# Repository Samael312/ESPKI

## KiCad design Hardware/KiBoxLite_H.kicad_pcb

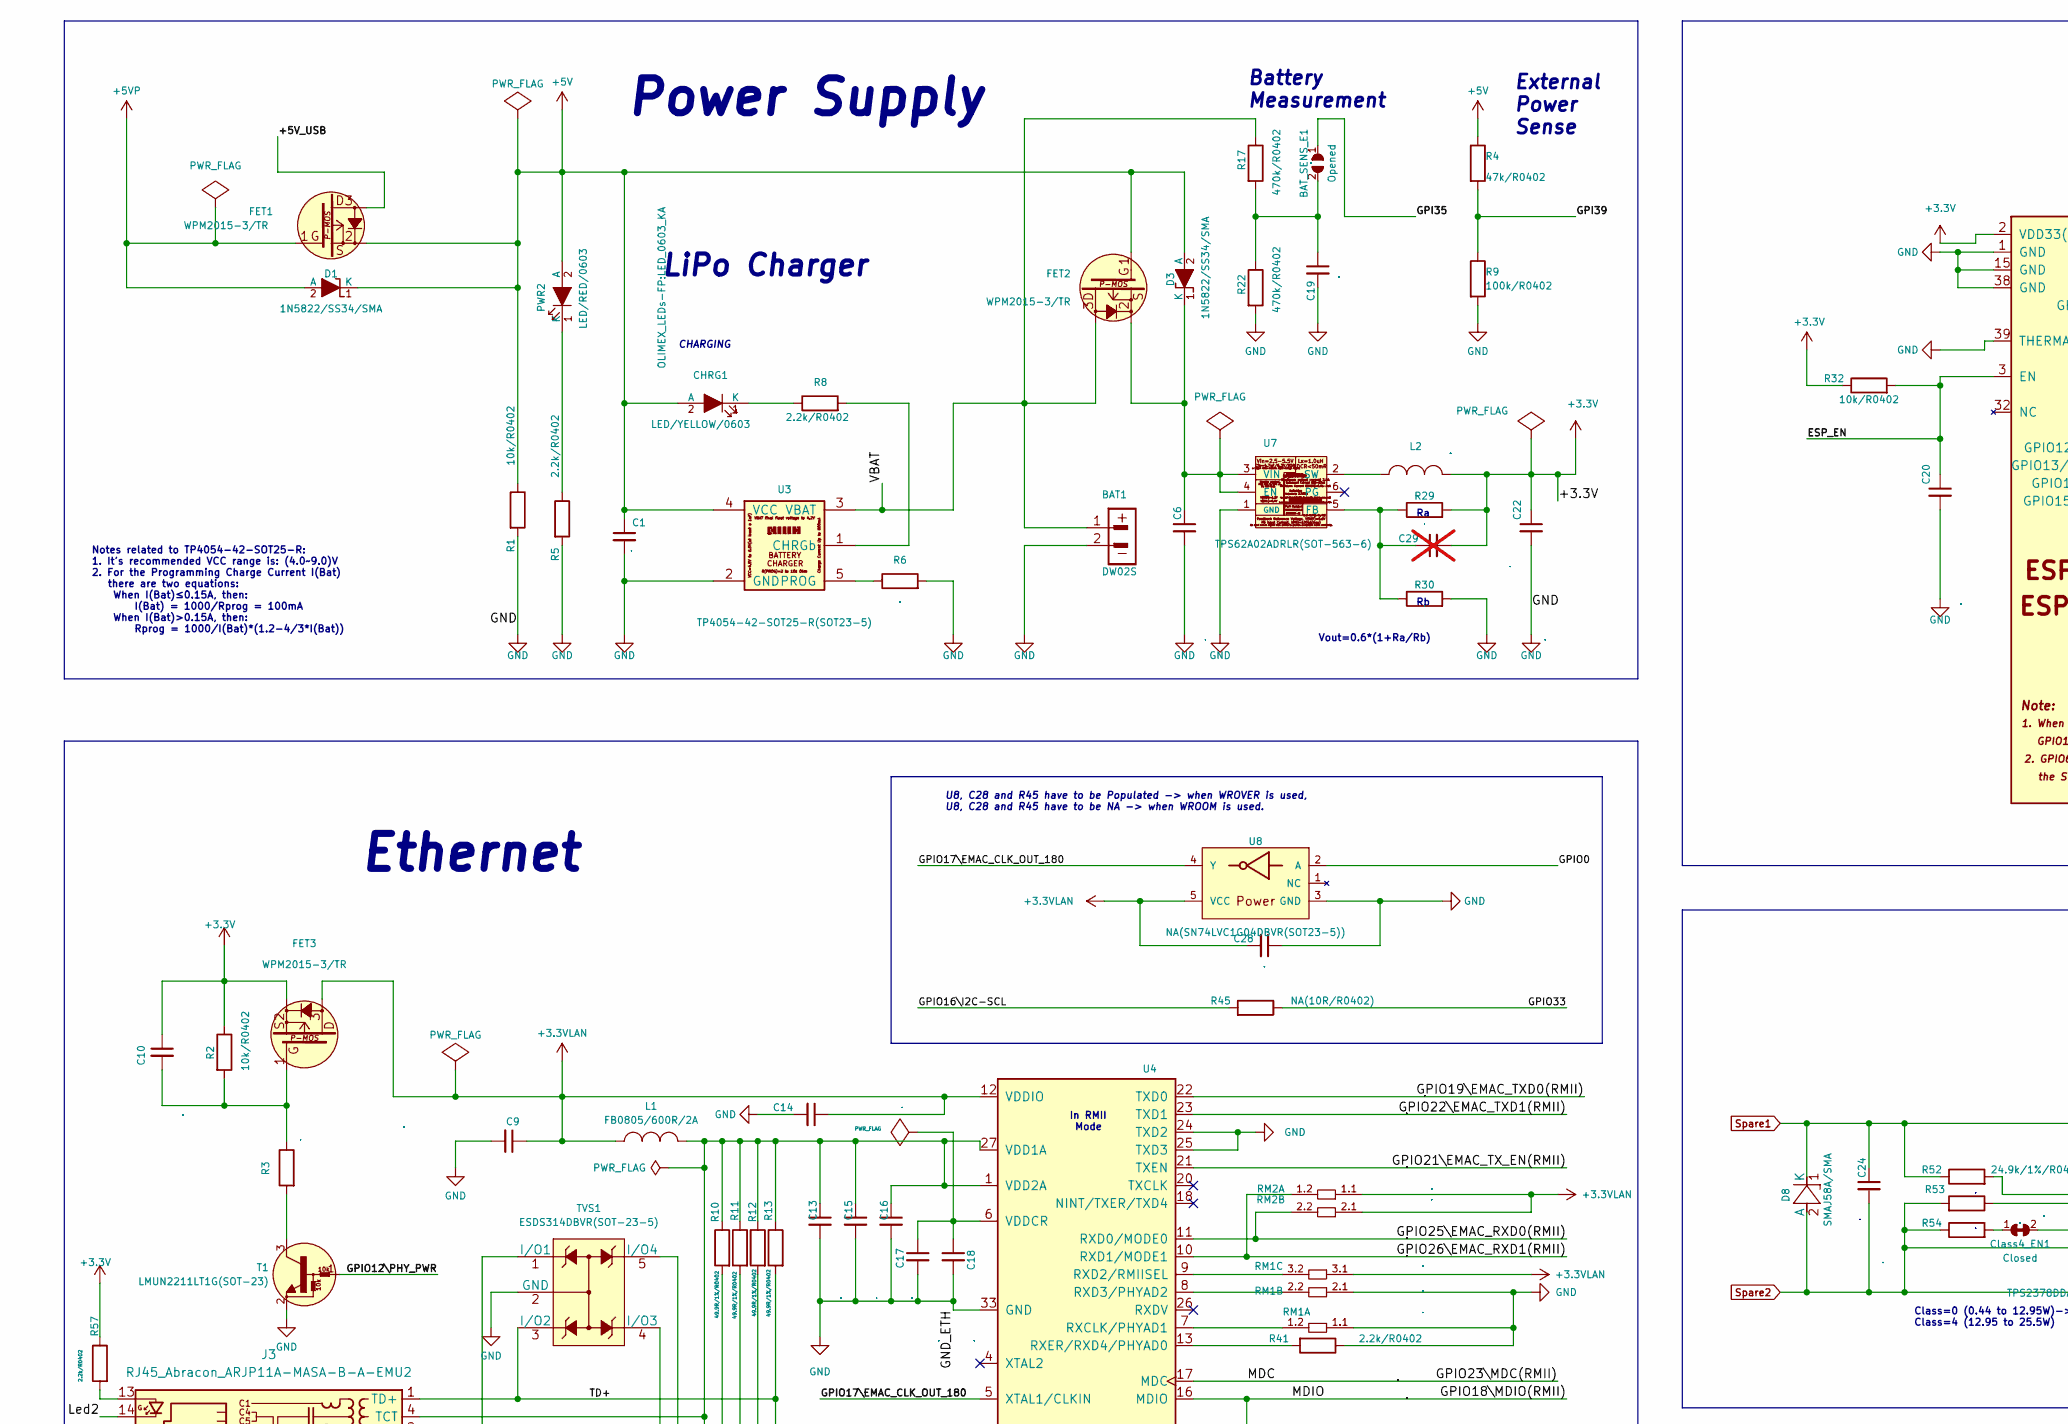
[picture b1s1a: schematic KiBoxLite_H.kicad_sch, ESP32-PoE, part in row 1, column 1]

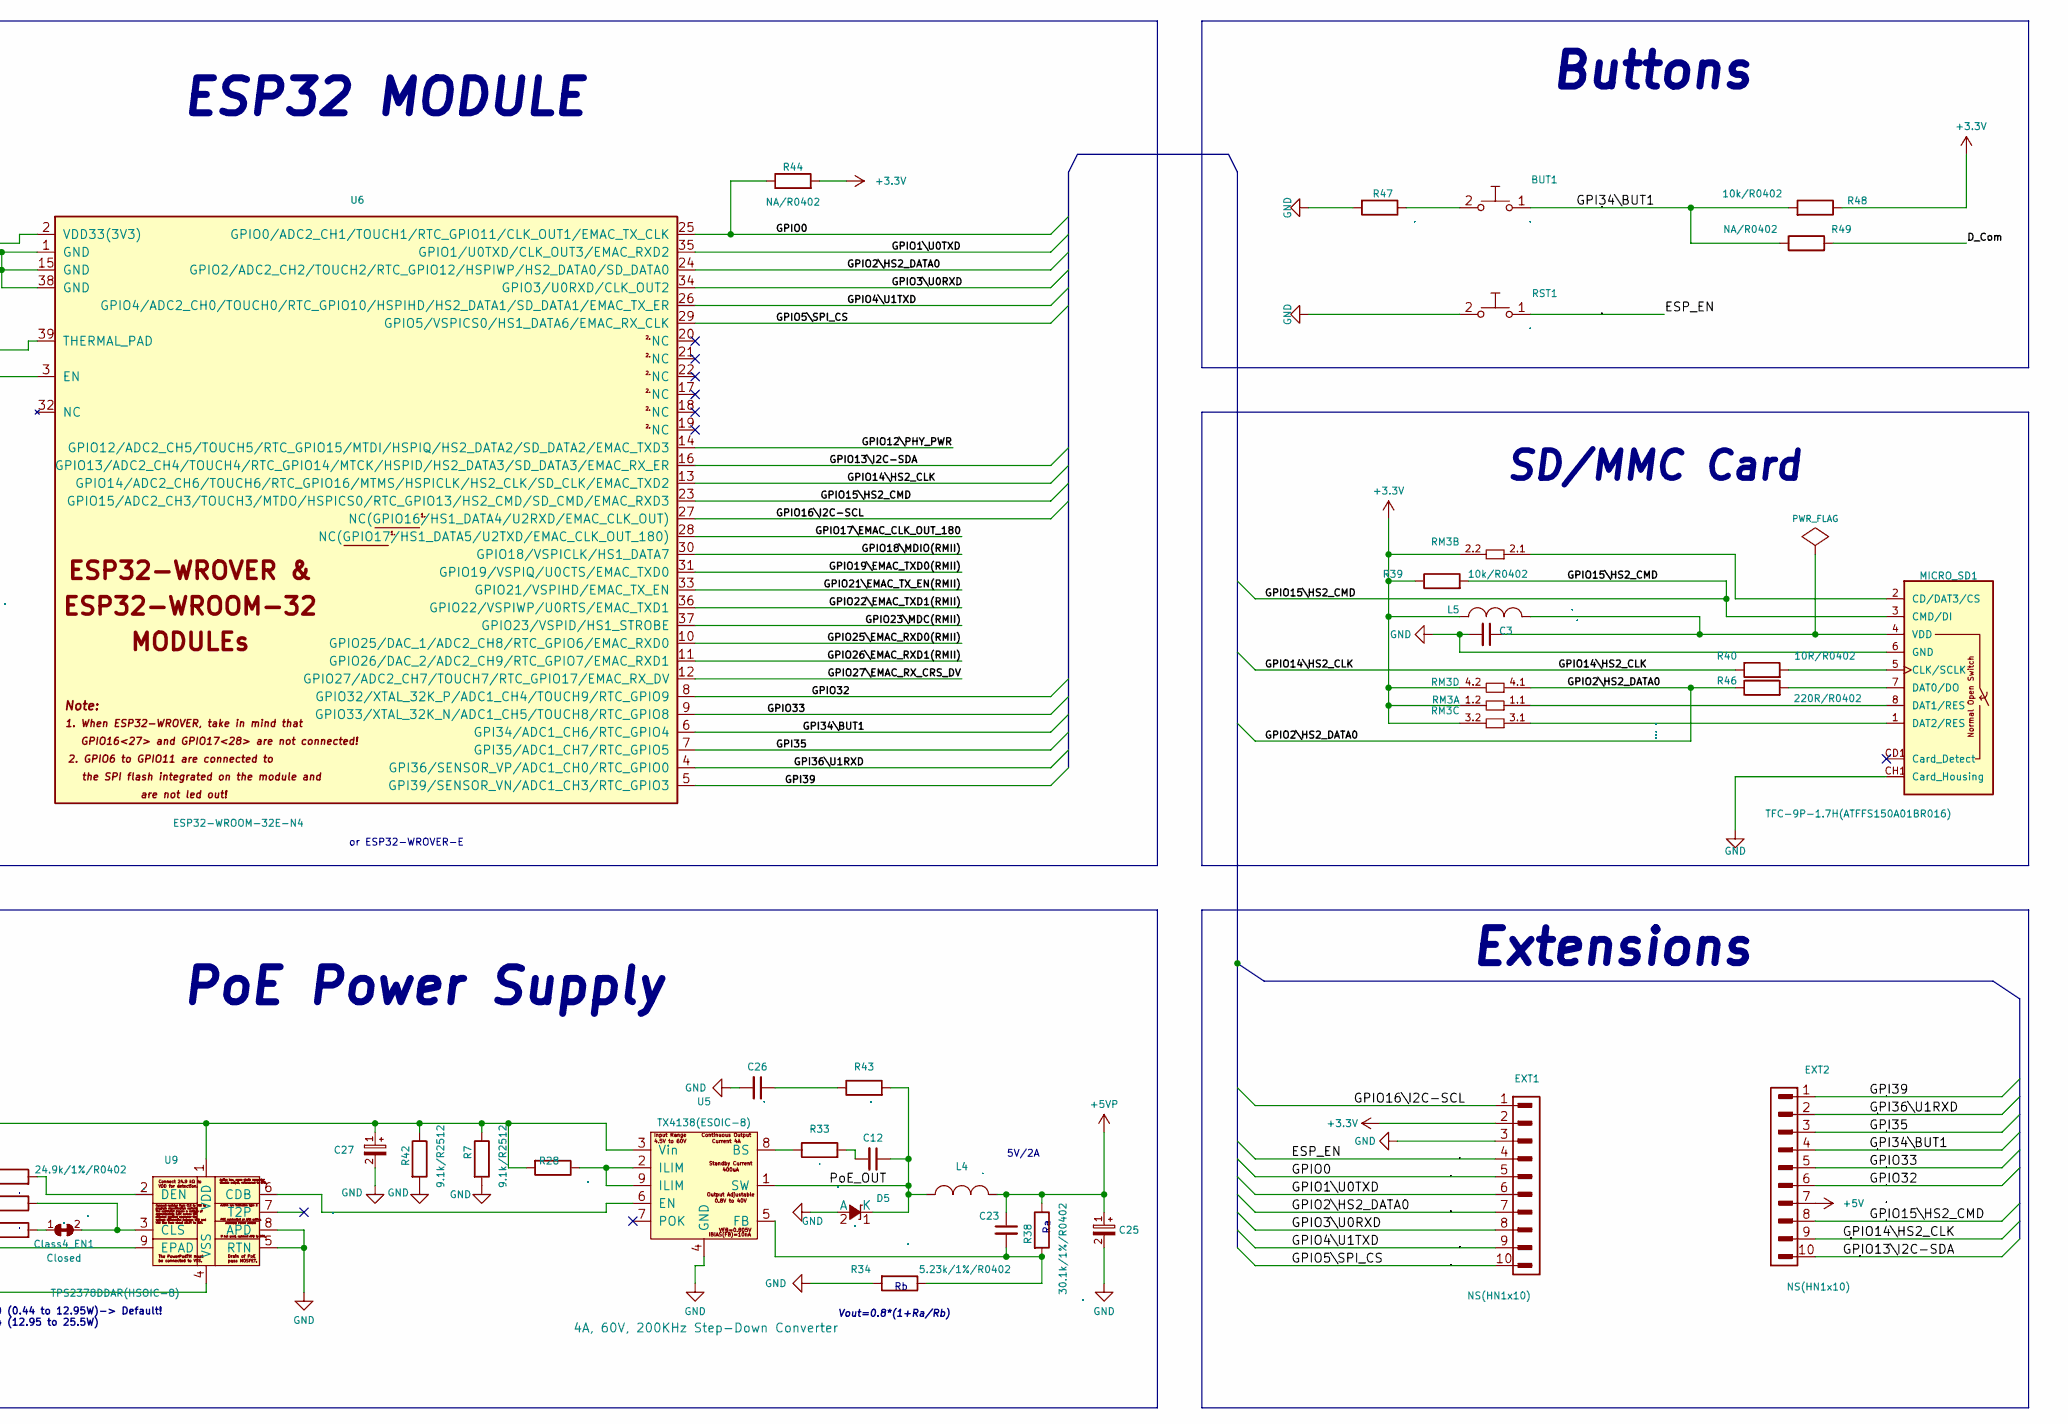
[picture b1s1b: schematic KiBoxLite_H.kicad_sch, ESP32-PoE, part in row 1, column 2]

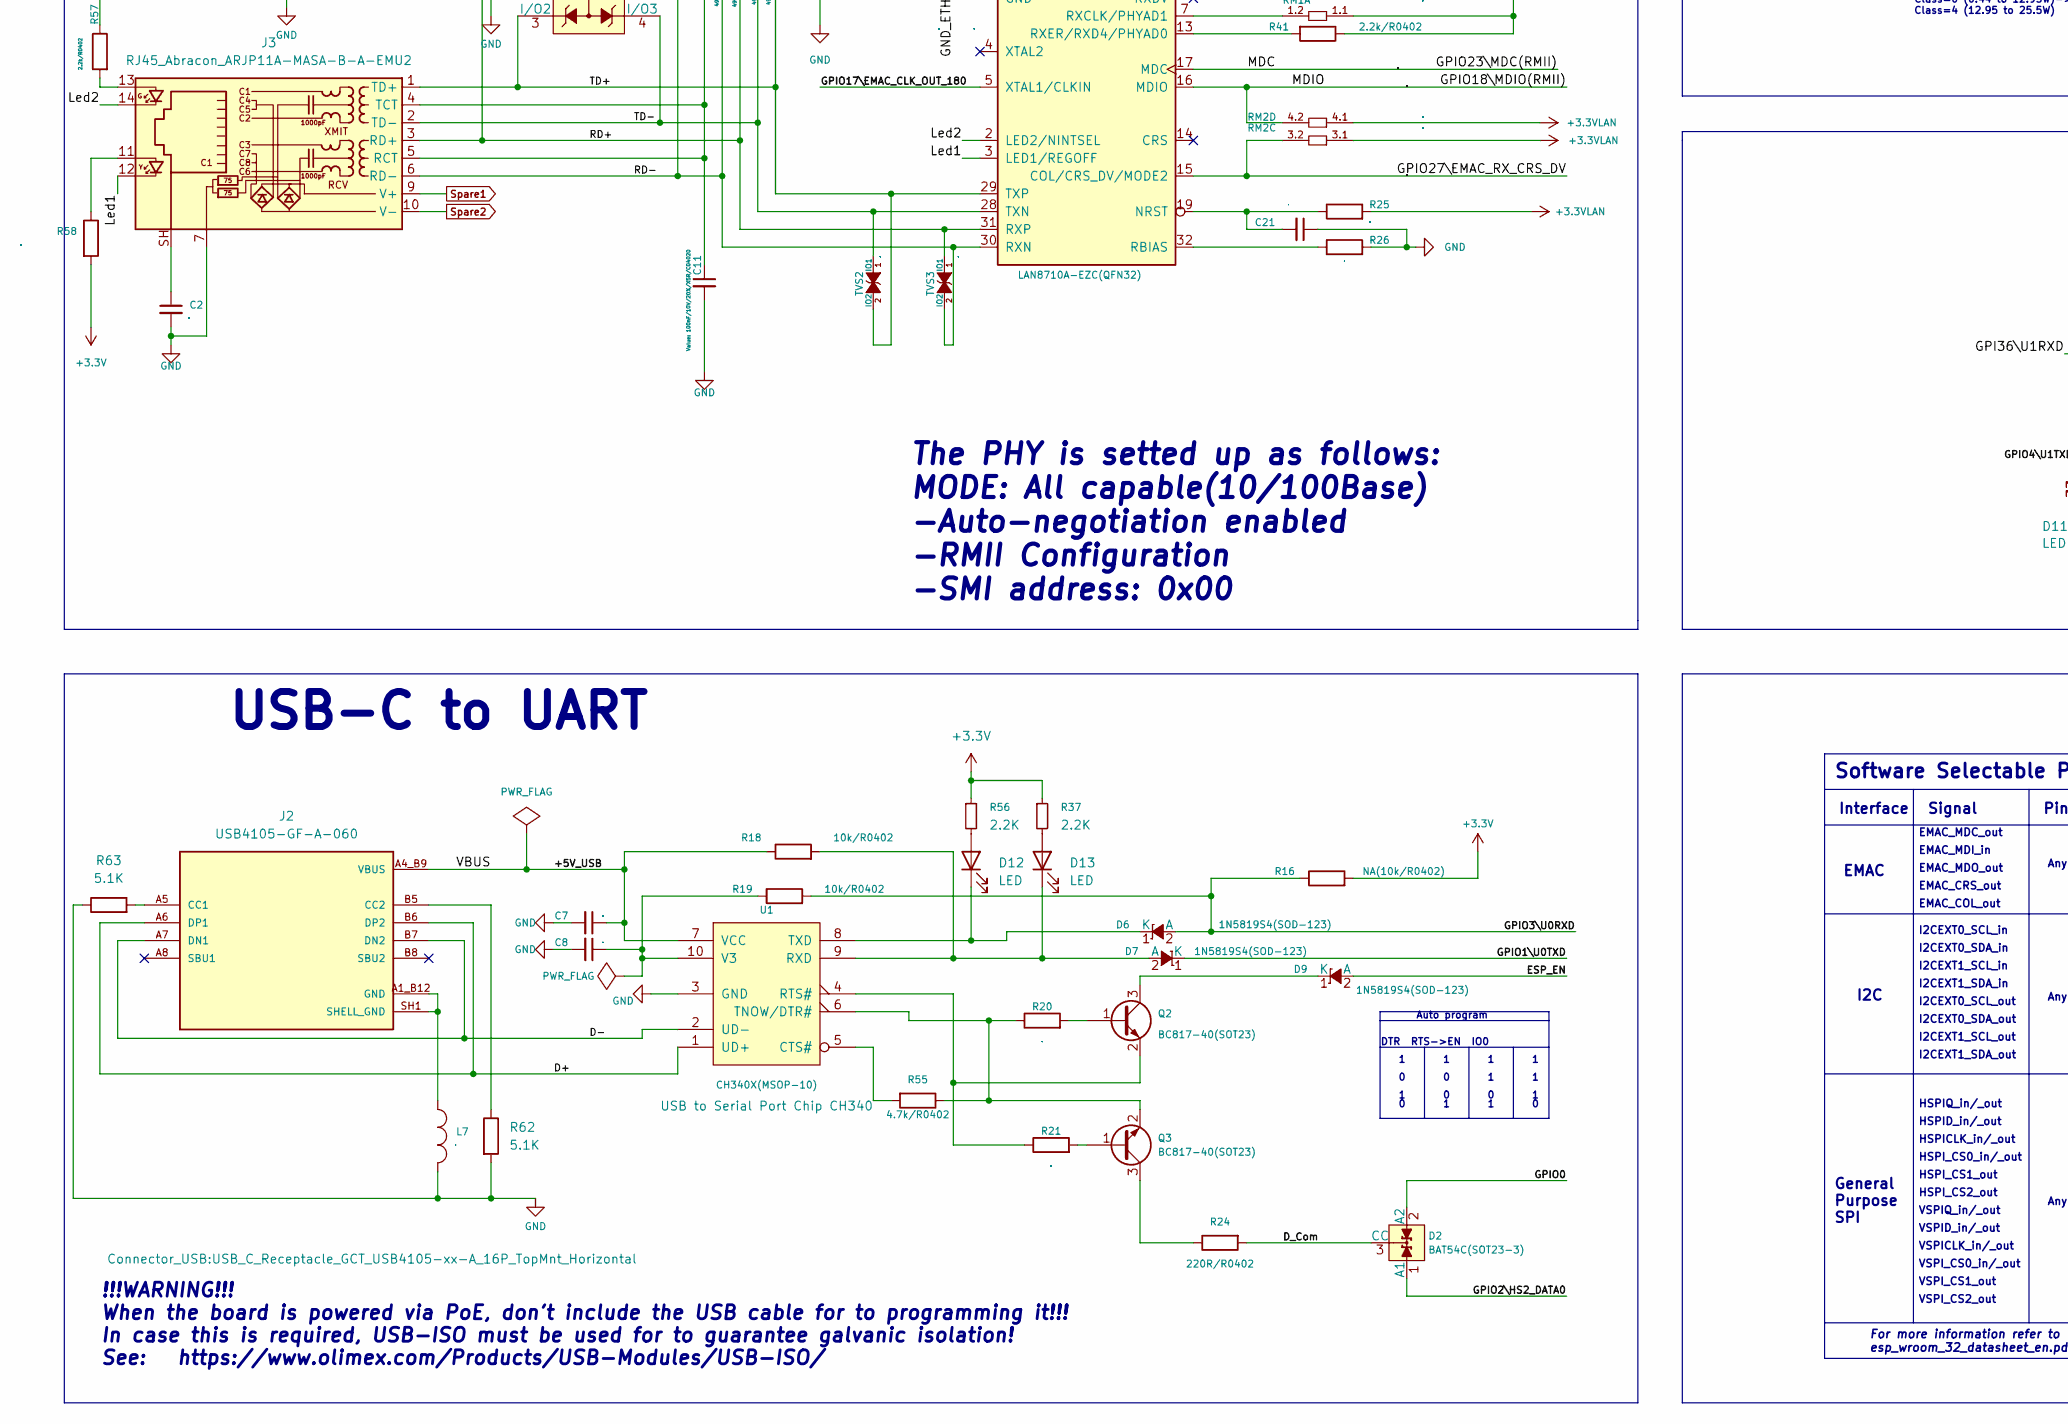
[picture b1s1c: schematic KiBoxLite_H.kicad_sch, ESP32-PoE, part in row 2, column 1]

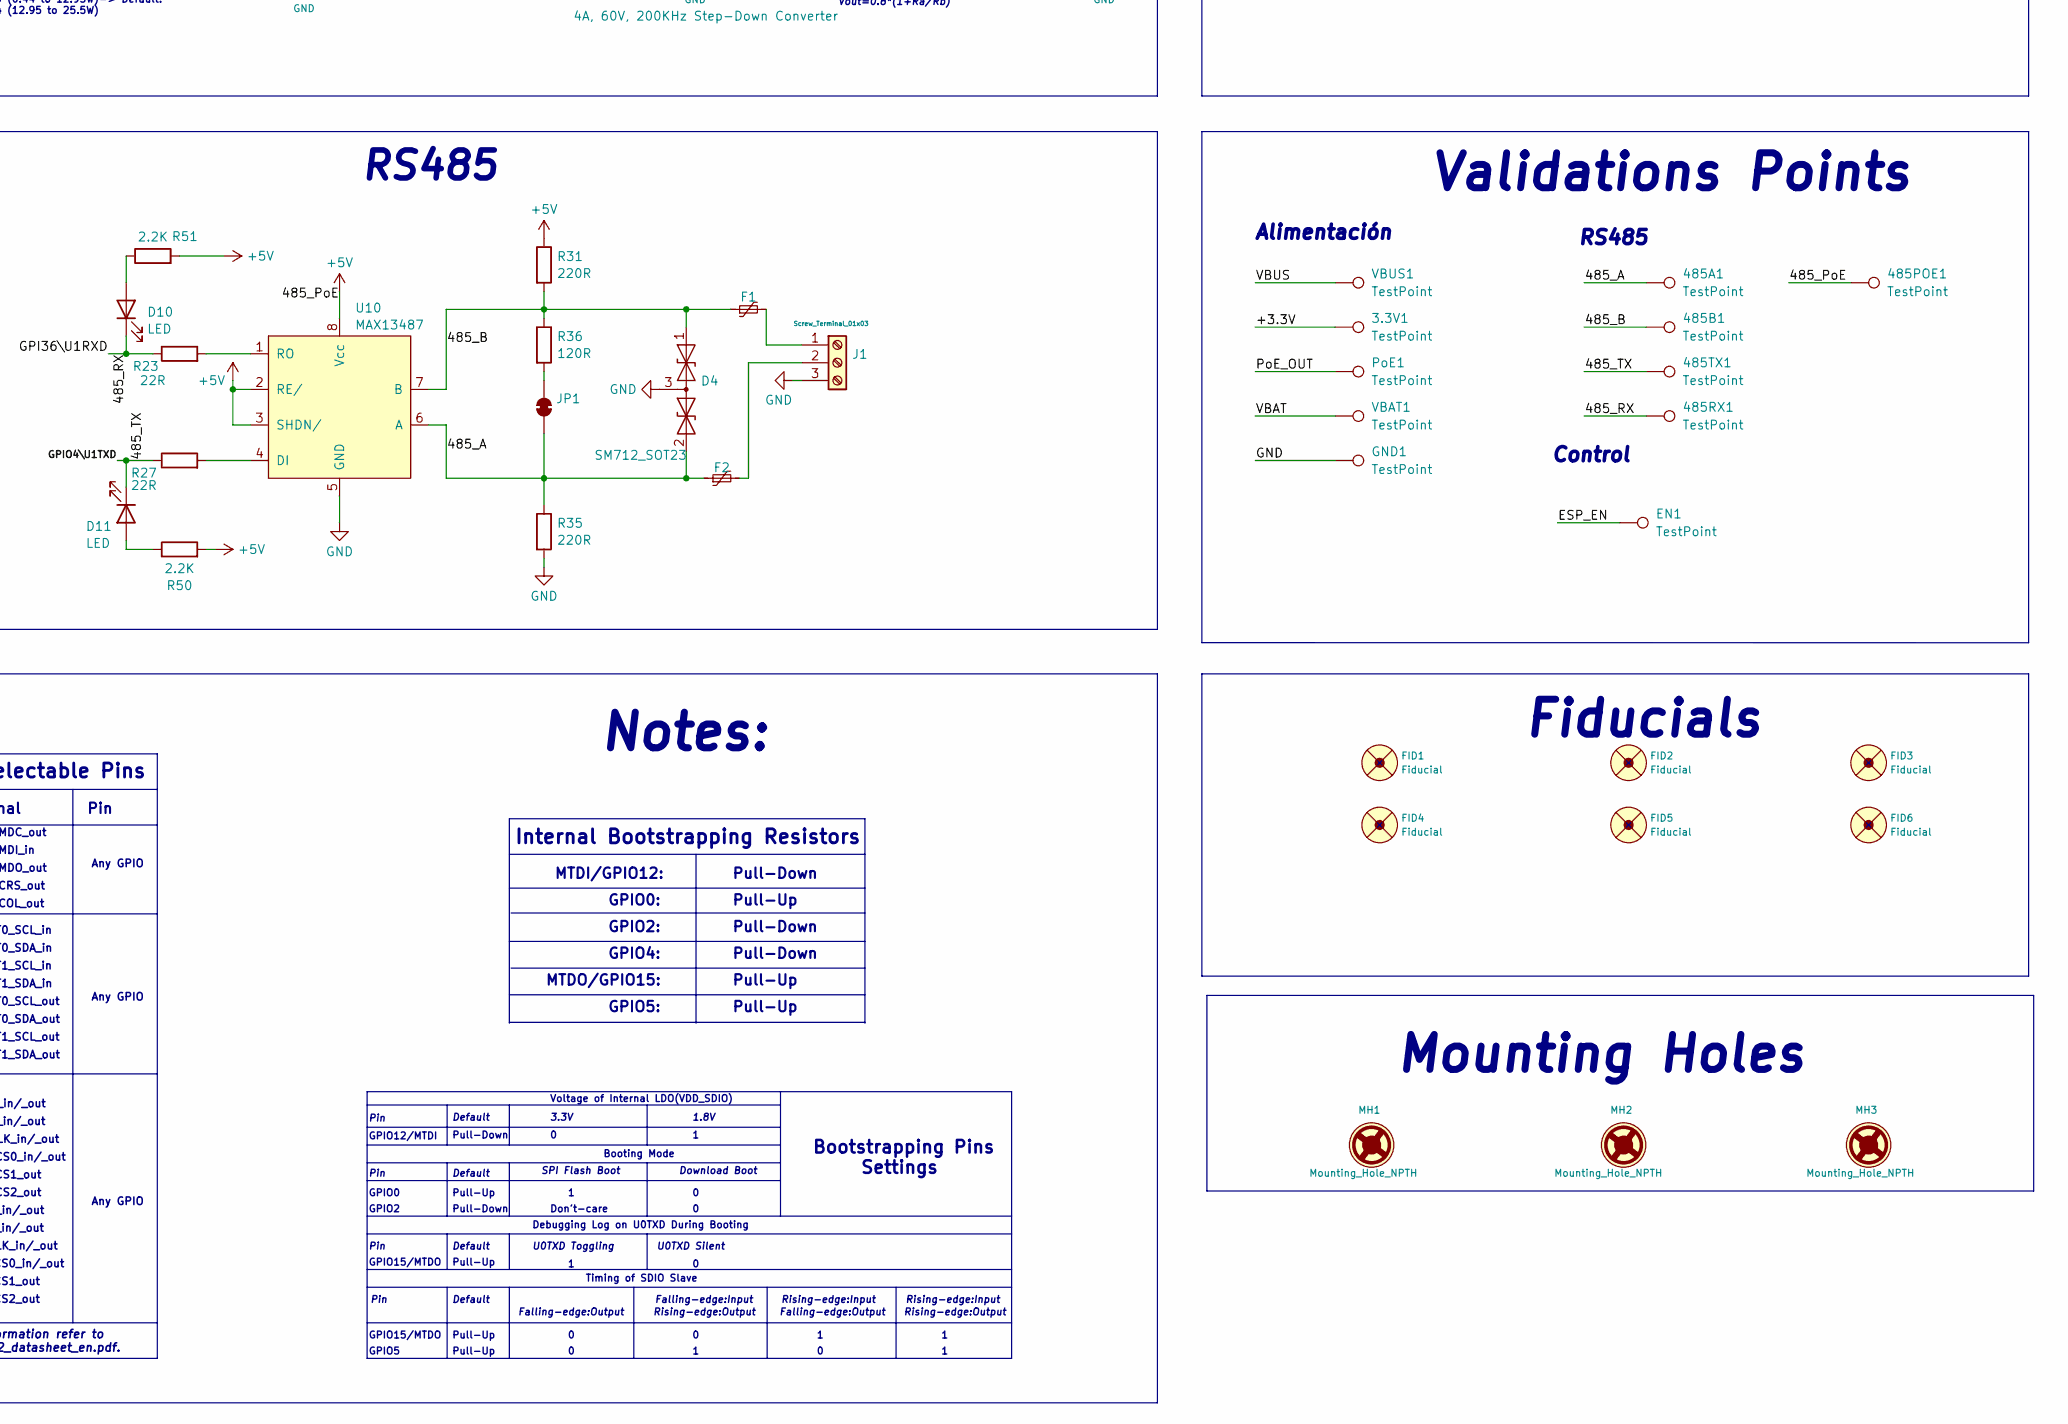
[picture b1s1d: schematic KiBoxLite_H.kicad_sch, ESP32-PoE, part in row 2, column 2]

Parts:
3.3V1, 485A1, 485B1, 485POE1, 485RX1, 485TX1: TestPoint; TestPoint_Pad_1.0x1.0mm
BAT1: DW02S; LIPO_BAT_VERTICAL_DW02S
BAT_SENS_E1: Opened; SJ
BUT1: IT1185AU2; IT1185AU2_V2
C1, C6, C7, C9, C10, C13, C22: 22uF/6.3V/20%/X5R/C0603; C_0603_5MIL_DWS
C2: 1nF/2000V/10%/X7R/C1206; C_1206_5MIL_DWS_ISO
C3: 47uF/6.3V/20%/X5R/C0805; C_0805_5MIL_DWS
C8, C11, C14, C15, C16, C18: 100nF/10V/20%/X5R/C04020; C_0402_5MIL_DWS
C12, C24: 100nF/100V/10%/X7R/C0603; C_0603_5MIL_DWS
C17: 2.2uF/6.3V/10%/X5R/C0603; C_0603_5MIL_DWS
C19: 1nF/50V/10%/X7R/C0402; C_0402_5MIL_DWS
C20: 1uF/10V/20%/X5R/C0603; C_0603_5MIL_DWS
C21: NA(10uF/6.3V/20%/X5R/C0603); C_0603_5MIL_DWS
C23: 12pF/50V/5%/COG/C0402; C_0402_5MIL_DWS
C25: 470uF/10V/20%/Low_ESR/RM2.5/6.0x11mm; CPOL-RM2.5mm_6.3x11mm_PTH
C26: NA(220pF/100V/C0603); C_0603_5MIL_DWS
C27: 15uF/100V/20%/RM2.5/6.3x11mm(Farnell:1281844); CPOL-RM2.5mm_6.3x11mm_PTH
C28: NA(100nF/10V/20%/X5R/C04020); C_0402_5MIL_DWS
C29: NA(120pF/50V/5%/C0G/C0402); C_0402_5MIL_DWS; not fitted
CHRG1: LED/YELLOW/0603; LED_0603_KA
Class4_EN1: Closed; SJ
D1, D3: 1N5822/SS34/SMA; SMA-KA
D2: BAT54C(SOT23-3); SOT23-3
D4: SM712_SOT23; SOT-23
D5: SS510/100V/5A/0.85V/DO214AB(SMC); DO214AB(SMC)_1(K)-2(A)
D6, D7, D9: 1N5819S4(SOD-123); SOD-123_1C-2A_KA
D8: SMAJ58A/SMA; SMA-KA
D10, D11, D12, D13: LED; LED_0201_0603Metric
EN1: TestPoint; TestPoint_Pad_1.0x1.0mm
EXT1, EXT2: NS(HN1x10); HN1x10
F1, F2: Polyfuse_Small; TS250
FET1, FET2, FET3: WPM2015-3/TR; SOT23
FID1, FID2, FID3, FID4, FID5, FID6: Fiducial; Fiducial1x3
GND1: TestPoint; TestPoint_Pad_1.0x1.0mm
J1: Screw_Terminal_01x03; PhoenixContact_MSTBA_2,5_3-G_1x03_P5.00mm_Horizontal
J2: USB4105-GF-A-060; USB_C_Receptacle_GCT_USB4105-xx-A_16P_TopMnt_Horizontal; PARTREV B3
J3: RJ45_Abracon_ARJP11A-MASA-B-A-EMU2; RJ45_Abracon_ARJP11A-MA_Horizontal
JP1: SolderJumper_2_Bridged; SolderJumper_IND_Data
L1, L5, L7: FB0805/600R/2A; L_0805_5MIL_DWS
L2: 1.0uH/4.2A/DCR=35mR/20%/2.00x1.60x1.00mm/L2016(PI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; L_2016_MM
L4: 33uH/2.1A/DCR=0.1R/20%/DBS135(PD3316MT330); DBS135
MH1, MH2, MH3: Mounting_Hole_NPTH; NPTH_2.2mm
MICRO_SD1: TFC-9P-1.7H(ATFFS150A01BR016); uSD(TFC-9P-1.xH(ATFFS150A01BR016))
PWR2: LED/RED/0603; LED_0603_KA
PoE1: TestPoint; TestPoint_Pad_1.0x1.0mm
Q2, Q3: BC817-40(SOT23); SOT23
R1, R2, R6, R18, R19, R25, R32, R39, R48: 10k/R0402; R_0402_5MIL_DWS
R3, R20, R21: 1k/R0402; R_0402_5MIL_DWS
R4: 47k/R0402; R_0402_5MIL_DWS
R5, R8, R41, R57, R58: 2.2k/R0402; R_0402_5MIL_DWS
R7, R42: 9.1k/R2512; R_2512_MM_DWS
R9: 100k/R0402; R_0402_5MIL_DWS
R10, R11, R12, R13: 49.9R/1%/R0402; R_0402_5MIL_DWS
R16: NA(10k/R0402); R_0402_5MIL_DWS
R17, R22: 470k/R0402; R_0402_5MIL_DWS
R23, R27: 22R; R_0402_5MIL_DWS
R24, R46, R47: 220R/R0402; R_0402_5MIL_DWS
R26: 12.1k/1%/R0402; R_0402_5MIL_DWS
R28: 0.03R/1%/R1206; R_1206_5MIL_DWS
R29: 220k/R0402; R_0402_5MIL_DWS
R30: 49.9k/1%/R0402; R_0402_5MIL_DWS
R31, R35: 220R; R_0402_5MIL_DWS
R33: 4.7R/R0402; R_0402_5MIL_DWS
R34: 5.23k/1%/R0402; R_0402_5MIL_DWS
R36: 120R; R_0402_5MIL_DWS
R37, R50, R51, R56: 2.2K; R_0402_5MIL_DWS
R38: 30.1k/1%/R0402; R_0402_5MIL_DWS
R40: 10R/R0402; R_0402_5MIL_DWS
R43: NA(22R/R0603); R_0603_5MIL_DWS
R44, R49: NA/R0402; R_0402_5MIL_DWS
R45: NA(10R/R0402); R_0402_5MIL_DWS
R52: 24.9k/1%/R0402; R_0402_5MIL_DWS
R53: 1.27k/1%/62.5mW/R0402; R_0402_5MIL_DWS
R54: NA(66.5R/1%/125mW/R0805); R_0805_5MIL_DWS
R55: 4.7k/R0402; R_0402_5MIL_DWS
R62, R63: 5.1K; R_0402_5MIL_DWS
RM1, RM2, RM3: RA1206_(4X0603)_4B8_2.2k; R_MATRIX_4
RST1: IT1185AU2; IT1185AU2_V2
T1: LMUN2211LT1G(SOT-23); SOT23
TVS1: ESDS314DBVR(SOT-23-5); SOT-23-5
TVS2, TVS3: NA(GG0402052R542P); D_0402_5MIL_DWS
U1: CH340X(MSOP-10); MSOP-10_Pitch-0.5mm_3.00x3.00x1.00mm
U3: TP4054-42-SOT25-R(SOT23-5); SOT-23-5
U4: LAN8710A-EZC(QFN32); QFN32_EP(33)_5.00x5.00x0.90mm_Pitch_0.50mm
U5: TX4138(ESOIC-8); ESOIC-8
U6: ESP32-WROOM-32E-N4; ESP32-WROVER(WROOM)-UNIVERSAL_MODULE
U7: TPS62A02ADRLR(SOT-563-6); SOT-563-6
U8: NA(SN74LVC1G04DBVR(SOT23-5)); SOT-23-5
U9: TPS2378DDAR(HSOIC-8); ESOIC-8
U10: MAX13487
VBAT1: TestPoint; TestPoint_Pad_1.0x1.0mm
VBUS1: TestPoint; TestPoint_Pad_1.0x1.0mm

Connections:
+3.3V: 3.3V1.1 (1_1), C10.1, C22.1, C29.2, EXT1.2, FET3.2, L2.2, L5.1, R2.1, R16.2, R29.2, R32.1, R37.1, R39.1, R44.2, R48.1, R56.1, R57.1, R58.2, RM3.1.2, RM3.2.2, RM3.3.2, RM3.4.2, U6.2 (VDD33(3V3))
+3.3VLAN: C9.1, C14.1, C28.2, FET3.3, L1.1, R25.2, RM1.3.1, RM2.1.1, RM2.2.1, RM2.3.1, RM2.4.1, U4.12 (VDDIO), U8.5 (VCC)
+5V: 485POE1.1 (1_1), C1.1, CHRG1.2 (A), D1.1 (K), D3.2 (A), EXT2.7, FET1.2, FET2.1, PWR2.2 (A), R1.1, R4.1, R31.1, R50.2, R51.2, U3.4 (VCC), U10.2 (RE/), U10.3 (SHDN/), U10.8 (Vcc)
+5VP: C23.1, C25.1 (+), D1.2 (A), FET1.1, L4.2, R38.1
/485_A: 485A1.1 (1_1), D4.2 (A2), F2.1, JP1.1 (A), R35.1, U10.6 (A)
/485_B: 485B1.1 (1_1), D4.1 (A1), F1.1, R31.2, R36.1, U10.7 (B)
/485_RX: 485RX1.1 (1_1), D10.1 (K), EXT2.2, R23.1, U6.4 (GPI36/SENSOR_VP/ADC1_CH0/RTC_GPIO0)
/485_TX: 485TX1.1 (1_1), D11.1 (K), EXT1.9, R27.1, U6.26 (GPIO4/ADC2_CH0/TOUCH0/RTC_GPIO10/HSPIHD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)
/D+: J2.A6 (DP1), J2.B6 (DP2), U1.1 (UD+)
/D-: J2.A7 (DN1), J2.B7 (DN2), U1.2 (UD-)
/D_Com: D2.3 (CC), R24.2, R49.2
/ESP_EN: C20.1, D9.2 (A), EN1.1 (1_1), EXT1.4, R32.2, RST1.1, U6.3 (EN)
/GPI34\BUT1: BUT1.1, EXT2.4, R48.2, R49.1, U6.6 (GPI34/ADC1_CH6/RTC_GPIO4)
/GPI35: BAT_SENS_E1.1, EXT2.3, U6.7 (GPI35/ADC1_CH7/RTC_GPIO5)
/GPI39: EXT2.1, R4.2, R9.1, U6.5 (GPI39/SENSOR_VN/ADC1_CH3/RTC_GPIO3)
/GPIO0: D2.2 (A2), EXT1.5, R44.1, U6.25 (GPIO0/ADC2_CH1/TOUCH1/RTC_GPIO11/CLK_OU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), U8.2 (A)
/GPIO1\U0TXD: D7.1 (K), EXT1.6, U6.35 (GPIO1/U0TXD/CLK_OUT3/EMAC_RXD2)
/GPIO2\HS2_DATA0: D2.1 (A1), EXT1.7, R46.1, RM3.4.1, U6.24 (GPIO2/ADC2_CH2/TOUCH2/RTC_GPIO12/HSPIWP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)
/GPIO3\U0RXD: D6.2 (A), EXT1.8, R16.1, R19.2, U6.34 (GPIO3/U0RXD/CLK_OUT2)
/GPIO5\SPI_CS: EXT1.10, U6.29 (GPIO5/VSPICS0/HS1_DATA6/EMAC_RX_CLK)
/GPIO12\PHY_PWR: T1.1 (B), U6.14 (GPIO12/ADC2_CH5/TOUCH5/RTC_GPIO15/MTDI/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)
/GPIO13\I2C-SDA: EXT2.10, U6.16 (GPIO13/ADC2_CH4/TOUCH4/RTC_GPIO14/MTCK/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)
/GPIO14\HS2_CLK: EXT2.9, R40.1, U6.13 (GPIO14/ADC2_CH6/TOUCH6/RTC_GPIO16/MTMS/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)
/GPIO15\HS2_CMD: EXT2.8, MICRO_SD1.3 (CMD/DI), R39.2, U6.23 (GPIO15/ADC2_CH3/TOUCH3/MTDO/HSPICS0/RTC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)
/GPIO16\I2C-SCL: EXT1.1, R45.2, U6.27 (NC(GPIO16/HS1_DATA4/U2RXD/EMAC_CLK_OUT))
/GPIO17\EMAC_CLK_OUT_180: U4.5 (XTAL1/CLKIN), U6.28 (NC(GPIO17/HS1_DATA5/U2TXD/EMAC_CLK_OUT_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), U8.4 (Y)
/GPIO18\MDIO(RMII): RM2.4.2, U4.16 (MDIO), U6.30 (GPIO18/VSPICLK/HS1_DATA7)
/GPIO19\EMAC_TXD0(RMII): U4.22 (TXD0), U6.31 (GPIO19/VSPIQ/U0CTS/EMAC_TXD0)
/GPIO21\EMAC_TX_EN(RMII): U4.21 (TXEN), U6.33 (GPIO21/VSPIHD/EMAC_TX_EN)
/GPIO22\EMAC_TXD1(RMII): U4.23 (TXD1), U6.36 (GPIO22/VSPIWP/U0RTS/EMAC_TXD1)
/GPIO23\MDC(RMII): U4.17 (MDC), U6.37 (GPIO23/VSPID/HS1_STROBE)
/GPIO25\EMAC_RXD0(RMII): RM2.2.2, U4.11 (RXD0/MODE0), U6.10 (GPIO25/DAC_1/ADC2_CH8/RTC_GPIO6/EMAC_RX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)
/GPIO26\EMAC_RXD1(RMII): RM2.1.2, U4.10 (RXD1/MODE1), U6.11 (GPIO26/DAC_2/ADC2_CH9/RTC_GPIO7/EMAC_RX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)
/GPIO27\EMAC_RX_CRS_DV: RM2.3.2, U4.15 (COL/CRS_DV/MODE2), U6.12 (GPIO27/ADC2_CH7/TOUCH7/RTC_GPIO17/EMAC_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)
/GPIO32: EXT2.6, U6.8 (GPIO32/XTAL_32K_P/ADC1_CH4/TOUCH9/RTC_G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)
/GPIO33: EXT2.5, R45.1, U6.9 (GPIO33/XTAL_32K_N/ADC1_CH5/TOUCH8/RTC_G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)
/Led1: J3.12, U4.3 (LED1/REGOFF)
/Led2: J3.14, U4.2 (LED2/NINTSEL)
/PoE_OUT: C12.1, D5.1 (K), L4.1, PoE1.1 (1_1), R43.2, U5.1 (SW)
/RD+: J3.3 (RD+), R11.2, TVS1.1 (I/O1), TVS3.1 (IO1), U4.31 (RXP)
/RD-: J3.6 (RD-), R10.2, TVS1.5 (I/O4), TVS3.2 (IO2), U4.30 (RXN)
/TD+: J3.1 (TD+), R13.2, TVS1.3 (I/O2), TVS2.2 (IO2), U4.29 (TXP)
/TD-: J3.2 (TD-), R12.2, TVS1.4 (I/O3), TVS2.1 (IO1), U4.28 (TXN)
/VBAT: BAT1.1, FET2.3, R17.1, U3.3 (VBAT), VBAT1.1 (1_1)
unnamed: BAT_SENS_E1.2, C19.1, R17.2, R22.1
unnamed: BUT1.2, R47.1
unnamed: C2.1, J3.SH
unnamed: C10.2, FET3.1, R2.2, R3.1
unnamed: C12.2, R33.2
unnamed: C26.1, R43.1
unnamed: CHRG1.1 (K), R8.1
unnamed: Class4_EN1.1, R54.2
unnamed: C6.1, D3.1 (K), FET2.2, U7.3 (VIN), U7.4 (EN)
unnamed: D9.1 (K), Q2.3 (C)
unnamed: D10.2 (A), R51.1
unnamed: D11.2 (A), R50.1
unnamed: D12.2 (A), R56.2
unnamed: D6.1 (K), D12.1 (K), U1.8 (TXD)
unnamed: D13.2 (A), R37.2
unnamed: D7.2 (A), D13.1 (K), R18.2, U1.9 (RXD)
unnamed: F1.2, J1.1
unnamed: F2.2, J1.2
unnamed: J2.A5 (CC1), R63.2
unnamed: J2.B5 (CC2), R62.1
unnamed: J3.11, R58.1
unnamed: J3.13, R57.2
unnamed: C11.1, C13.1, C15.1, C16.1, J3.4 (TCT), J3.5 (RCT), L1.2, R10.1, R11.1, R12.1, R13.1, U4.1 (VDD2A), U4.27 (VDD1A)
unnamed: JP1.2 (B), R36.2
unnamed: MICRO_SD1.2 (CD/DAT3/CS), RM3.2.1
unnamed: MICRO_SD1.5 (CLK/SCLK), R40.2
unnamed: MICRO_SD1.7 (DAT0/DO), R46.2
unnamed: MICRO_SD1.8 (DAT1/RES), RM3.1.1
unnamed: MICRO_SD1.1 (DAT2/RES), RM3.3.1
unnamed: C3.1, L5.2, MICRO_SD1.4 (VDD)
unnamed: PWR2.1 (K), R5.1
unnamed: Q2.1 (B), R20.2
unnamed: Q2.2 (E), R21.1, U1.4 (RTS#)
unnamed: Q3.1 (B), R21.2
unnamed: Q3.3 (C), R24.1
unnamed: Q3.2 (E), R20.1, R55.1, U1.6 (TNOW/DTR#)
unnamed: R28.1, U5.2 (ILIM), U5.9 (ILIM)
unnamed: R3.2, T1.3 (C)
unnamed: R55.2, U1.5 (CTS#)
unnamed: C8.1, R19.1, U1.10 (V3)
unnamed: R8.2, U3.1 (CHRGb)
unnamed: R6.1, U3.5 (PROG)
unnamed: C21.2, R25.1, U4.19 (NRST)
unnamed: R26.1, U4.32 (RBIAS)
unnamed: RM1.1.2, U4.7 (RXCLK/PHYAD1)
unnamed: RM1.3.2, U4.9 (RXD2/RMIISEL)
unnamed: RM1.2.2, U4.8 (RXD3/PHYAD2)
unnamed: R41.2, U4.13 (RXER/RXD4/PHYAD0)
unnamed: C17.1, C18.1, U4.6 (VDDCR)
unnamed: R33.1, U5.8 (BS)
unnamed: U5.6 (EN), U9.6 (CDB)
unnamed: C23.2, R34.1, R38.2, U5.5 (FB)
unnamed: C29.1, R29.1, R30.1, U7.5 (FB)
unnamed: L2.1, U7.2 (SW)
unnamed: Class4_EN1.2, R53.1, U9.3 (CLS)
unnamed: R52.2, U9.2 (DEN)
unnamed: R27.2, U10.4 (DI)
unnamed: R23.2, U10.1 (RO)
Spare1: C24.1, C27.1 (+), D8.1 (K), J3.9 (V+), R7.1, R28.2, R42.1, R52.1, U5.3 (Vin), U9.1 (VDD)
Spare2: C24.2, D8.2 (A), J3.10 (V-), R53.2, R54.1, U9.4 (VSS), U9.9 (EPAD)
VBUS: C7.1, FET1.3, J2.A4_B9 (VBUS), J2.B4_A9 (VBUS), R18.1, U1.7 (VCC), VBUS1.1 (1_1)

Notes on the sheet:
HSPI_CS1_out
Pull-Down
EMAC_MDO_out
HSPI_CS2_out
GPIO4:
Falling-edge:Output
Control
EMAC
I2CEXT0_SDA_out
Default
MTDO/GPIO15:
For more information refer to esp_wroom_32_datasheet_en.pdf.
Rprog
VSPICLK_in/_out
PoE Power Supply
Fiducials
HSPIQ_in/_out
Interface
DTR RTS->EN IO0
Pull-Up
CHARGING
Any GPIO
The PHY is setted up as follows: MODE: All capable(10/100Base) -Auto-negotiation enabled -RMII Configuration -SMI address: 0x00
LiPo Charger
VSPI_CS2_out
VSPI_CS0_in/_out
HSPID_in/_out
VSPID_in/_out
Pin
VSPIQ_in/_out
I2CEXT1_SDA_in
Buttons
I2CEXT0_SCL_out
MTDI/GPIO12:
I2CEXT1_SCL_in
GPIO5
SPI Flash Boot
Vout=0.6*(1+Ra/Rb)
RDET
HSPI_CS0_in/_out

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

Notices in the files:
Hardware/KiBoxLite_H.kicad_pcb:
(C) 2025
